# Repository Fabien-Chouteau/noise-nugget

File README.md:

# noise-nugget
Square Inch music widget

Noise Nugget is a compact digital synthesizer based on an 180MHz Cortex-M4 and
quality audio DAC with headphone amplifier.

My goal with this project is to create a little "Swiss Army knife" of audio
synthesis. Packing the maximum features on the smallest and cheapest board.

With all its connectivity (USB, 2 x audio out, 1 x audio in, I2C, UART, GPIOs)
it can be used for many different tasks:
 - Digital synthesizer, with a MIDI interface or some other means of control
 - Audio effects, for a guitar pedal or synthesizer (delay, reverb, distortion)
 - Audio FX trigger board, playing pre-recorded sounds
 - Audio playback, recording sounds from the input and then playing it back at
   the push of a button
 - USB sound interface

So far I implemented one audio effect, a MIDI over USB synth and sampler. Noise
Nugget is a compact digital synthesizer based on an 180MHz Cortex-M4 and
quality audio DAC with headphone amplifier.

My goal with this project is to create a little "Swiss Army knife" of audio
synthesis. Packing the maximum features on the smallest and cheapest board.

With all its connectivity (USB, 2 x audio out, 1 x audio in, I2C, UART, GPIOs)
it can be used for many different tasks:
- Digital synthesizer, with a MIDI interface or some other means of control
- Audio effects, for a guitar pedal or synthesizer (delay, reverb, distortion)
- Audio FX trigger board, playing pre-recorded sounds
- Audio playback, recording sounds from the input and then playing it back at
  the push of a button
- USB sound interface

So far I implemented one audio effect, a MIDI over USB synth and sampler.

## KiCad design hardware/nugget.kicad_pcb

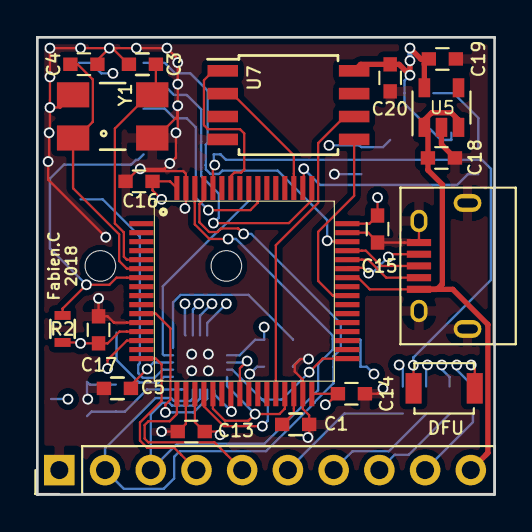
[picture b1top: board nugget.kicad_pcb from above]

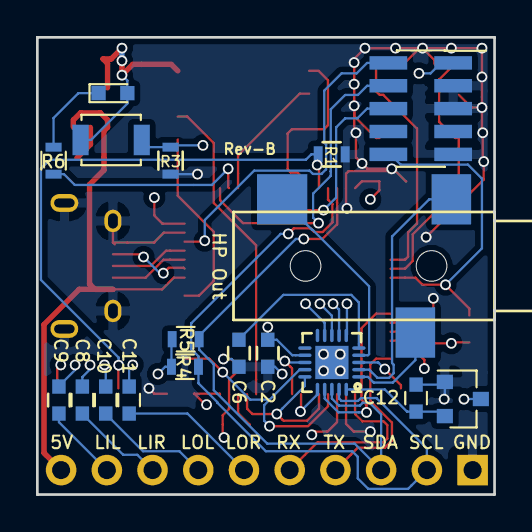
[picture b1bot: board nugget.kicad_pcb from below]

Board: 4 copper layers, 25.4 x 25.4 mm, 38 parts (18 on the bottom side), 43 nets.

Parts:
C1, C8, C9, C10, C11, C18, C19: 2.2uF; C_0603
C2, C5, C6, C12, C13, C14, C15, C16, C17, C20: 100nF; C_0603
C3, C4: 20pF; C_0603
D1: LED_Small; LED_0603
DFU1: EVQ-P2K02Q; SW_SPST_B3U-1000P
J1: CONN_01X10; Pin_Header_Straight_1x10_Pitch2.54mm
J2: 10118194; USB_Micro-B
J3: CONN_02X05; Socket_Strip_Straight_2x05_Pitch1.27mm_SMD
R1, R2, R3, R4, R5: 10K; R_0603
R6: 510R; R_0603
SW1: EVQ-P2K02Q; SW_SPST_B3U-1000P
U1: SGTL5000; UQFN-20-1EP_3x3mm_Pitch0.4mm
U2: AP7313-18SRG-7; SOT-23
U3: SJ-3523-SMT
U4: STM32F446RET; LQFP64
U5: AP2112K-3.3TRG1; SOT-23-5
U7: SST26VF064B-104V/SM; SOIJ-8_5.3x5.3mm_Pitch1.27mm
Y1: ABM3B-8.000MHZ-B2-T; Crystal_SMD_0603_4Pads

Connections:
1V8: C12.1, U1.20, U2.2
3V3: C2.1, C5.1, C13.2, C14.2, C15.2, C16.2, C17.2, C19.1, C20.1, D1.2, DFU1.2, J3.1, R2.1, R4.1, R5.1, SW1.2, U1.3, U1.12, U2.3, U4.13, U4.19, U4.32, U4.48, U4.64, U5.5, U7.8
AUDIO_SCL: J1.2, R4.2, U1.19, U4.61
AUDIO_SDA: J1.3, R5.2, U1.18, U4.62
GND: C1.2, C2.2, C3.2, C4.2, C5.2, C6.2, C12.2, C13.1, C14.1, C15.1, C16.1, C17.1, C18.2, C19.2, C20.2, J1.1, J2.5, J2.6, J3.3, J3.5, J3.9, R1.2, R3.2, U1.21, U2.1, U4.12, U4.18, U4.31, U4.47, U4.63, U5.2, U7.4, Y1.2, Y1.4
I2S_DIN: U1.17, U4.11
I2S_DOUT: U1.16, U4.23
I2S_LRCLK: U1.14, U4.20, U4.33
I2S_MCLK: U1.13, U4.24
I2S_SCLK: U1.15, U4.21, U4.29
LED1: R6.2, U4.50
LINE_IN_L: C8.2, J1.9
LINE_IN_R: C9.2, J1.8
LINE_OUT_L: C10.2, J1.7
LINE_OUT_R: C11.2, J1.6
NRESET: J3.10, R2.2, U4.7
unnamed: C3.1, U4.5, Y1.3
unnamed: C4.1, U4.6, Y1.1
unnamed: C6.1, U1.5
unnamed: C8.1, U1.9
unnamed: C9.1, U1.8
unnamed: C10.1, U1.7
unnamed: C11.1, U1.6
unnamed: D1.1, R6.1
unnamed: DFU1.1, R1.1, U4.60
unnamed: U1.1, U3.3
unnamed: U1.2, U3.2
unnamed: U1.4, U3.1
QSPI_BK1_IO0: U4.40, U7.5
QSPI_BK1_IO1: U4.51, U7.2
QSPI_BK1_NCS: U4.58, U7.1
QSPI_CLK: U4.28, U7.6
SW1: R3.1, SW1.1, U4.14
SWDCLK: J3.4, U4.49
SWDIO: J3.2, U4.46
TDO: J3.6, U4.55
UART_RX: J1.5, U4.17
UART_TX: J1.4, U4.16
USB_D+: J2.3, U4.45
USB_D-: J2.2, U4.44
USB_ID: J2.4, U4.43
VBUS: C18.1, J1.10, J2.1, U4.42, U5.1, U5.3
VCAP1: C1.1, U4.30

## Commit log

2018-08-13 Noise Nugger rev-B
2018-09-03 First software demo
2018-09-06 Create two different modes synth and flanger fx
2018-09-30 Remove AdaCore's ADL submodule
2018-09-30 Switch to my version of ADL with proto USB support
2018-09-30 Add MIDI over USB control
2018-10-07 Add sampler mode
2018-10-07 Add sampler mode (#1)
2018-10-20 Add rev-B schematics
2018-10-21 Add rev-B pictures
